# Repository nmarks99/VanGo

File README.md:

# VanGo: A Drawing Robot
VanGo is a differential drive robot that can draw SVG images on a page.

First, an SVG image is converted to XY coordinates using this online tool: [Coordinator](https://spotify.github.io/coordinator/).
Then, using these XY coordinates, a trajectory of waypoints is generated for the robot to follow.
Trajectory tracking is implemented using a simple PID steering control algorithm, and the robot determines its pose in space
through wheel odometry, using quadrature encoders on the motors. For more in-depth information, please see the VanGo documentation
at [https://nmarks99.github.io/VanGo/](https://nmarks99.github.io/VanGo/). VanGo is still relatively early in development
and several aspects of the project need more work and fine tuning, such as the trajectory tracking algorithm, a command line interface
for the client application, and improved mechanical design. However, in its current state, VanGo demonstrates a good proof of concept.

## Project Structure
- `vango-firmware` is the firmware for the ESP32 board based on [esp-idf-hal](https://github.com/esp-rs/esp-idf-hal)
- `vango-client` is a desktop command line application for controlling the robot
- `vango-utils` is a utility library used by both the firmware and client.
- `hardware` directory contains the KiCAD project for the PCB

## Future Development
This project also uses another library I have developed, [diff-drive](https://github.com/nmarks99/diff-drive),
primarily for pose estimation via wheel odometry. In the future I hope to use both the VanGo and diff-drive projects
as starting points for developing a general purpose, high-performance, and open-source, differential drive robot
that anyone can build with firmware based on Rust on the ESP32 (think DIY [TurtleBot](https://www.robotis.us/turtlebot-3/)).

## Other Notes
One of my biggest motivations for this project was to learn more rust programming, particularly embedded rust, which is why
this project is 100% rust code 🦀. Like mostly everyone else, I've primarily used C and C++ for programming microcontrollers
in the past, most of the time using the Arduino framework together with PlatformIO which I've found to be a very pleasant
experience. After having worked on this project for several months, using Rust on the ESP32, I've found it to be a
equally pleasant experience, after some intial growing pains. Below are some of my opinions on the state of embedded Rust.
Note this is generally with regards to Rust on ESP [(esp-rs)](https://github.com/esp-rs), however some of it applies to embedded
Rust in a broader sense.

**The Good**
- Using `esp-idf-hal` you get to program the ESP32 in Rust (almost) as if you were writing a program on your desktop
This means you get to take full advantage of the Rust standard library and mostly any external crates you may need.
- Using Cargo works the same as it would in your other Rust projects and integrates seamlessly with flashing the board.
you can see in my vango-firmware/.cargo/config.toml file, I created an alias `cargo flash` to flash the board from the
command line and also set the partition table (sets how much space in memory you are reserving for your program):
`flash = "espflash --release --partition-table partitions.csv"`
- As in the case for non-embedded Rust, if the code compiles it almost always just works, which is super nice, especially
for embedded projects where you not only have to build, but also flash the board. I've found that bugs are often very easy
to track down in Rust. The only subtle error I encountered, and it's not even that subtle, is that if you accidentally
enter a loop that is doing nothing but looping, it will probably trigger the watchdog timer and continually reset the board.
There is a way to disable the WDT, but you can also just add a short delay (1ms even is enough) if you are in a loop doing
nothing.

**The Bad**
- Finding example code is (unsurpisingly since Arduino is much more mature) a little difficult compared to Arduino.
For example, I had a very tough time finding an example of how to do some basic things like GPIO interrpts
and timer based interrupts, which I could find examples for very easily in Arduino. However, after figuring it out,
a timer interrupt in `esp-idf-hal` turns out to be almost as easy to use as the popular [IntervalTimer](https://www.pjrc.com/teensy/td_timing_IntervalTimer.html)
in Arduino. Another thing that was very tough to find example code for was bluetooth. Eventually I found [esp32-nimble](https://github.com/taks/esp32-nimble)
which works quite well and isn't too complicated. The developer is was also quick to reply to an issue I opened for an additional feature.
- Flashing the board takes *forever*. I haven't timed it but it probably takes like a minute or two maybe which is much longer than similar Arduino
programs. This may just be something specific to my project, but it was fairly annoying to wait for the board to be flashed whenever I made updates.

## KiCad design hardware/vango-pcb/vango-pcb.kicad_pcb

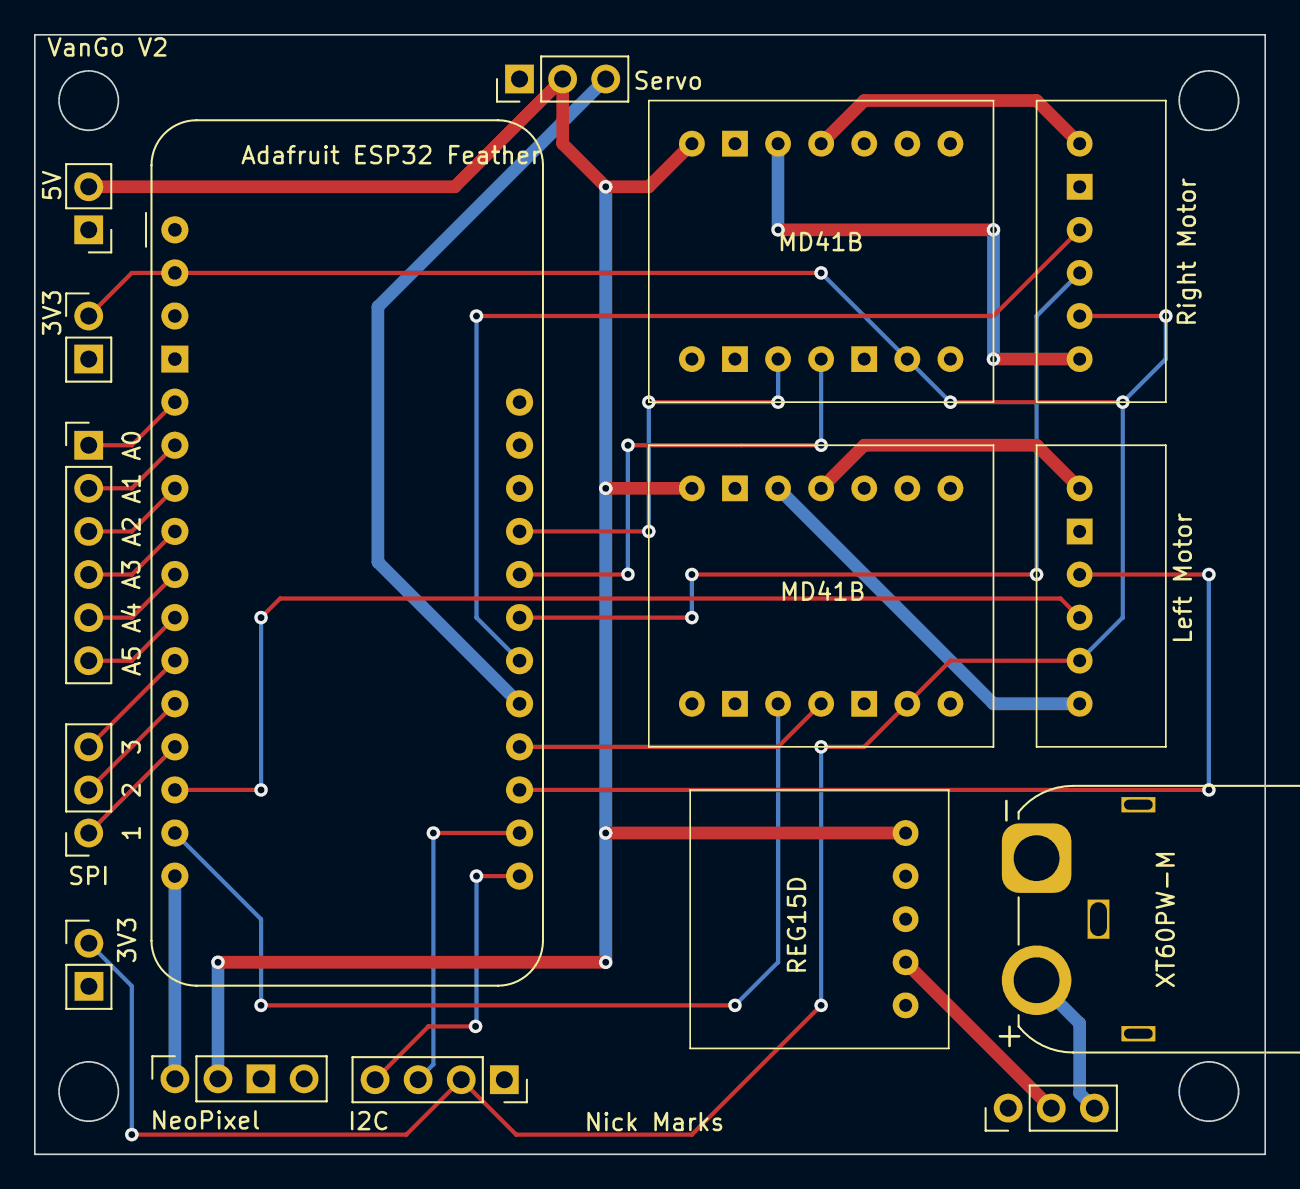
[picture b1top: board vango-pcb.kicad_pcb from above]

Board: 2 copper layers, 72.5 x 66.0 mm, 16 parts (0 on the bottom side), 30 nets.

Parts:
3V3: Conn_01x02; PinHeader_1x02_P2.54mm_Vertical
A1: Adafruit_Feather_HUZZAH32_ESP32; Adafruit_Feather
J1: XT60PW-M; AMASS_XT60IPW-M_1x03_P7.20mm_Horizontal
J2: NeoPixel; PinSocket_1x04_P2.54mm_Vertical
J3: I2C; PinSocket_1x04_P2.54mm_Vertical
J4: Conn_01x06; PinHeader_1x06_P2.54mm_Vertical
J5: SPI; PinSocket_1x03_P2.54mm_Vertical
J6, J7: Conn_01x02; PinHeader_1x02_P2.54mm_Vertical
SW1: SW_SPDT; PinHeader_1x03_P2.54mm_Vertical
Servo: SG90_Servo; PinHeader_1x03_P2.54mm_Vertical
U1, U3: MD41B
U2: REG15D
U4: Left Motor; N20_motor
U5: Right Motor; N20_motor

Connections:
+3V3: 3V3.1, A1.2 (3V3), J3.2, J6.1, U1.6 (~SLEEP), U3.6 (~SLEEP), U4.5 (VCC), U5.5 (VCC)
+5V: J2.2, J7.2, Servo.2, U1.8 (VIN), U2.5 (VOUT), U3.8 (VIN)
/A0: A1.5 (DAC2/A0), J4.1
/A1: A1.6 (DAC1/A1), J4.2
/A2: A1.7 (I34/A2), J4.3
/A3: A1.8 (I39/A3), J4.4
/A4: A1.9 (IO36/A4), J4.5
/A5: A1.10 (IO4/A5), J4.6
/A8: A1.21 (A8/IO15), Servo.3
/IO12: A1.24 (A11/IO12), U3.4 (PH/IN2)
/IO13: A1.25 (A12/IO13), U3.3 (EN/IN1)
/IO14: A1.19 (A6/IO14), U4.3 (C1)
/IO16: A1.14 (RX/IO16), U4.4 (C2)
/IO17: A1.15 (TX/IO17), U1.3 (EN/IN1)
/IO27: A1.23 (A10/IO27), U5.4 (C2)
/IO32: A1.20 (A7/IO32), U1.4 (PH/IN2)
/IO33: A1.22 (A9/IO33), U5.3 (C1)
/MISO: A1.13 (MISO/IO19), J5.1
/MOSI: A1.12 (MOSI/IO18), J5.2
/SCK: A1.11 (SCK/IO5), J5.3
/SCL: A1.18 (SCL/IO22), J3.3
/SDA: A1.17 (SDA/IO23), J3.4
GND: 3V3.2, A1.4 (GND), J1.1 (-), J2.3, J3.1, J6.2, J7.1, Servo.1, U1.2 (GND), U1.5 (PMODE), U1.9 (GND), U2.3 (GND), U2.4 (GND), U3.2 (GND), U3.5 (PMODE), U3.9 (GND), U4.2 (GND), U5.2 (GND)
unnamed: A1.16 (IO21), J2.1
unnamed: J1.2 (+), SW1.3 (C)
unnamed: SW1.2 (B), U2.2 (VIN)
unnamed: U1.10 (OUT1), U4.6 (M2)
unnamed: U1.11 (OUT2), U4.1 (M1)
unnamed: U3.10 (OUT1), U5.6 (M2)
unnamed: U3.11 (OUT2), U5.1 (M1)

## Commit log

2023-06-19 basic blinky example works
2023-06-19 change nick to nick
2023-06-20 update gitignore, add client.rs for wifi client test
2023-06-20 add readme
2023-06-20 fix header typo
2023-06-20 update readmes
2023-06-20 add wifi keyboard controller code
2023-06-21 control servo with potentiometer
2023-06-22 add utils.rs
2023-06-23 motor + driver working, not interrupts yet
    - also added num-traits crate and almost_equal in utils.rs
2023-06-23 can read encoder ticks and millis()
2023-06-23 trying to add interrupts again
2023-06-23 interrupt code compiles
    needed to add
    "rustflags = ["-C", "default-linker-libraries"]" to cargo.toml
2023-06-23 interrupt code compiles
    needed to add
    "rustflags = ["-C", "default-linker-libraries"]" to .cargo/config.toml
2023-06-23 sike!, interrupt code does not work
    works in the training repo code but that is with a
    riscv esp32 chip. Building for the standard esp32
    is not working
2023-06-23 add proto dir for testing to gitignore
2023-06-23 remove client.rs
2023-06-24 actually got an ISR working I think!
2023-06-24 elapsed time looks reasonable
2023-06-24 doubling the speed roughly halves time
2023-06-24 added flag for interrupt so rpm=0 when not moving
2023-06-24 interrupt based speed control with potentiometer
2023-06-27 add neopixel library and test in main
2023-06-27 motor control with pot again
2023-06-29 Neopixel struct and adjustable brightness
2023-06-29 both motors with pot working
2023-06-29 minor updates
2023-06-29 basic pid loop and updated gear ratio
2023-06-30 started writing Motor struct
2023-07-03 add encoder.rs back
2023-07-04 RPM looks right with timer interrupt
2023-07-04 PID needs tuning
2023-07-06 renamed variables to left and right instead of 1 and 2
2023-07-06 fixed map function
    - can't do integer divisions like that...duhh!
2023-07-06 added Pen struct
    - creating pwm driver in struct works
    - pen up, down, and get_state methods work
2023-07-06 refactor some of pen.rs, remove motor.rs for now
    need to rewrite motor.rs similar to pen.rs and inlude PID
    controller in there
2023-07-10 add completed PCB, KiCAD project
    note the DRC (rules check) will give a warnings
    on the footprints not matching library symbols.
    This is because I manually changed the GND pads
    in the PCB editor to be square but didn't change
    them in the library
2023-07-13 start of the vango desktop client
2023-07-14 read and write csv works, basic setup started
2023-07-14 basic start to the client, add scripts dir
2023-07-14 decided I want to track scripts dir
2023-07-14 comment to outline main loop idea
2023-07-15 add wheel radius and separation
2023-07-16 BLE integrated into vango_client
2023-07-16 add termion stuff for keyboard control
2023-07-21 create Cluster and implementations of it
2023-07-21 clustering appears to work as intended
2023-07-21 clusterize function to make it even easier
    - rocket example doesn't seem to work exactly...
2023-07-22 update kicad pcb
2023-07-22 add servo connector, more space for voltage reg
2023-07-22 pcb should be all good now
2023-07-22 change text to be "Vango V2"
2023-07-22 add gerber files
2023-07-22 fix small typo
2023-07-22 Remove old wifi_kb_controller thing
2023-07-23 add ble service
2023-07-24 ble characteristic for left and right wheel speeds
2023-07-24 sending speed command with BLE works
    the 'hard' work is done with remote control,
    now lots of tidying up and implementing
    something like the ros teleop twist keyboard
2023-07-24 move regulator over more, move servo pins
2023-07-27 interrim commit, may be broken
2023-08-01 driving the robot in 'manual' mode worksgit add .!
2023-08-02 better log messages and added manual mode flag, utils.rs
2023-08-03 sending counts decoding and encoding almost works
2023-08-03 rename vango_client to vango-client
2023-08-03 rename vango to vango-firmware
2023-08-03 create vango-utils and replace utils.rs in vango-firmware
2023-08-03 replace utils.rs with vango-utils
2023-08-03 add tests, architecture specific int_to_bytes
2023-08-03 adjust docstring
2023-08-04 add tokio task in auto mode
2023-08-09 add updated nimble library and tested connection interval
2023-08-09 rename UUID, UUIDs are now consts, add debug mode to client
2023-08-09 tuning infrastructure good ish
    - testing setup for tuning works, the PID controller is whack
    - I think the problem is setting the direction
2023-08-10 motor speed control actually works now
    - decided to do much more in the timer ISR
    - using atomic floats now, not sure if thats a bad move but it works
2023-08-10 add speed control results. P control is sufficient it seems
2023-08-10 add speed_control_plot.py script
2023-08-10 move monitor.sh to scripts/
2023-08-10 attempted to write motor.rs, gave up
2023-08-11 tested in loop, with some diff_drive lib stuff
2023-08-11 anlges work now, needed to divide by ticks_per_rad
2023-08-11 robot can drive in a circle
    seems to drift a lot. Might be good to average or otherwise
    smooth the speed calculation
2023-08-11 minor adjustments
2023-08-12 forward works, not backward
2023-08-13 Forward working correctly
    revert to here if I break it when trying to do backwards
2023-08-13 MotorDirection enum, holding off on Motor struct etc for now
2023-08-13 backwards works, just need to flip sign of u
2023-08-13 both directions workgit add src/main.rs
2023-08-13 seems like some weird overshoot but maybe ok
2023-08-14 speed control works great, maybe a touch of overshoot.
2023-08-14 think I like the no-overshoot PD controller better, not too slow
2023-08-15 odometry works! do not normalize angle before using FK
2023-08-15 protection for when target speed flips sign
2023-08-15 add opposite signs
2023-08-15 add f32->ascii, ascii->f32 conversion functions
2023-08-15 update client to work with firmware since change to atomicf32
2023-08-15 pose characteristics in firmware and client
    logging info in the client not quite right yett
2023-08-15 manual control while displaying pose works
2023-08-16 fix direction changing issue
    needed to account for when the target speed was identically zero
2023-08-16 Remove old counts ble characteristics
2023-08-16 add docs with mdbook documentation
2023-08-16 add built site and remove gitignore, maybe a bad idea
2023-08-16 add github actions workflow to build docs
2023-08-16 oops, workflows should be in .github folder
2023-08-16 fix path to docs/book I think
2023-08-16 update docs
2023-08-17 commanding zero immediately sets duty to zero
2023-08-18 almost ready for drawing dev, need to fix pose.theta
    - happy enough with manual control performance for now
    - added servo BLE characteristic and tested it and it works well
    - added flashing neopixel for fun
2023-08-21 add neopixel Color enum, docs, remove motor.rs
2023-08-21 added trajectory.rs
2023-08-21 remove quick_plot.py
2023-08-21 add get_rotation_direction and normalize_to_range
2023-08-22 I think pose.theta is good enough, added low IQ tracking alg in client
2023-08-22 minor updates to docs, naive controller
2023-08-24 PID steering control works but it kinda sucks
2023-08-24 rectangle okay
2023-08-25 add oval and donut
2023-08-25 move images to src to see if that fixes it
2023-08-25 add firmware.md, remove dev
2023-08-28 save
2023-08-28 add images to docs overview and README
2023-08-28 fix readme image path
2023-08-28 change scale
2023-08-28 add video links to docs
